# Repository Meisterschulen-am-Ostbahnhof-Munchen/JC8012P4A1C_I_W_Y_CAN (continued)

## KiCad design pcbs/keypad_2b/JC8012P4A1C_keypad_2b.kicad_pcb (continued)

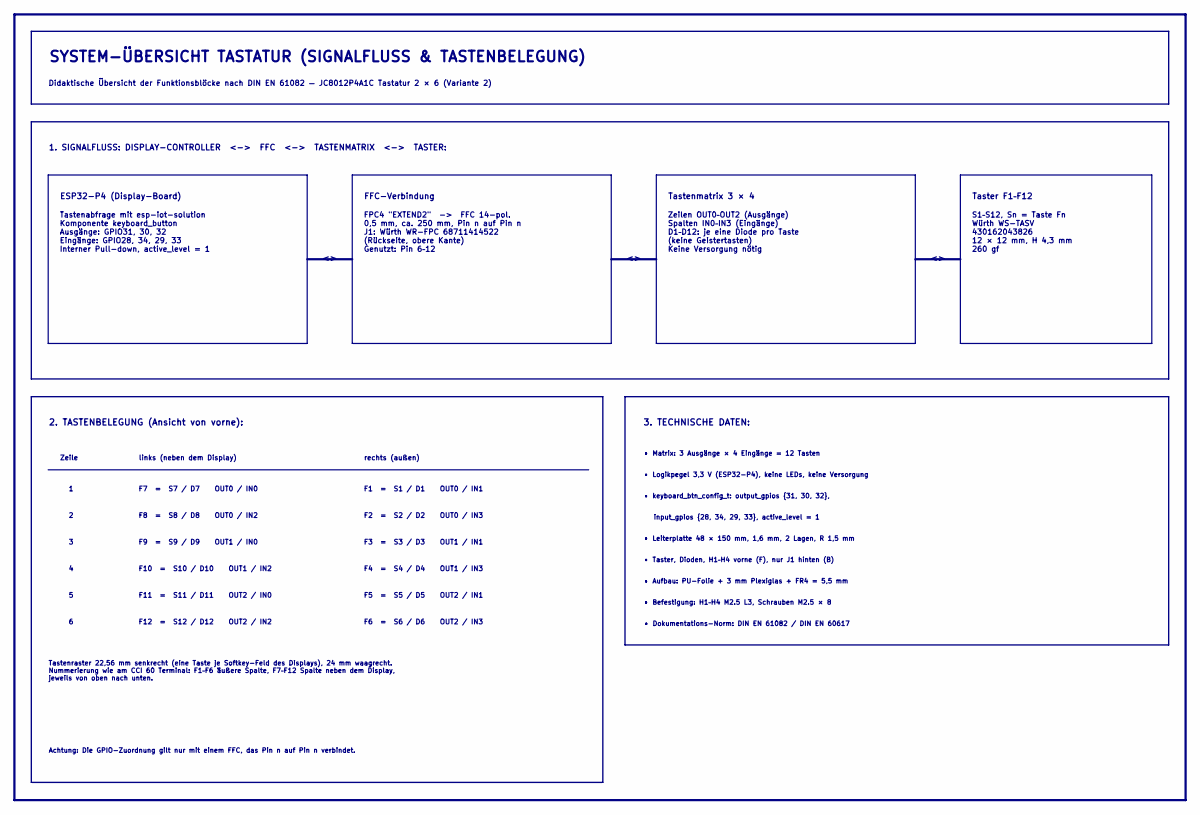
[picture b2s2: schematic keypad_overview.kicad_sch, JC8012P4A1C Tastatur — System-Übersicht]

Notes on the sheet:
• Befestigung: H1–H4 M2.5 L3, Schrauben M2.5 × 8
FPC4 "EXTEND2" -> FFC 14-pol. 0,5 mm, ca. 250 mm, Pin n auf Pin n J1: Würth WR-FPC 68711414522 (Rückseite, obere Kante) Genutzt: Pin 6–12
2. TASTENBELEGUNG (Ansicht von vorne):
F6 = S6 / D6 OUT2 / IN3
F3 = S3 / D3 OUT1 / IN1
Tastenraster 22,56 mm senkrecht (eine Taste je Softkey-Feld des Displays), 24 mm waagrecht. Nummerierung wie am CCI 60 Terminal: F1–F6 äußere Spalte, F7–F12 Spalte neben dem Display, jeweils von oben nach unten.
1. SIGNALFLUSS: DISPLAY-CONTROLLER <-> FFC <-> TASTENMATRIX <-> TASTER:
• keyboard_btn_config_t: output_gpios {31, 30, 32},
• Logikpegel 3,3 V (ESP32-P4), keine LEDs, keine Versorgung
Zeilen OUT0–OUT2 (Ausgänge) Spalten IN0–IN3 (Eingänge) D1–D12: je eine Diode pro Taste (keine Geistertasten) Keine Versorgung nötig
F5 = S5 / D5 OUT2 / IN1
F11 = S11 / D11 OUT2 / IN0
F9 = S9 / D9 OUT1 / IN0
F1 = S1 / D1 OUT0 / IN1
links (neben dem Display)
S1–S12, Sn = Taste Fn Würth WS-TASV 430162043826 12 × 12 mm, H 4,3 mm 260 gf
F12 = S12 / D12 OUT2 / IN2
Zeile
FFC-Verbindung
F4 = S4 / D4 OUT1 / IN3
• Leiterplatte 48 × 150 mm, 1,6 mm, 2 Lagen, R 1,5 mm
• Aufbau: PU-Folie + 3 mm Plexiglas + FR4 = 5,5 mm
F8 = S8 / D8 OUT0 / IN2
• Taster, Dioden, H1–H4 vorne (F), nur J1 hinten (B)
Achtung: Die GPIO-Zuordnung gilt nur mit einem FFC, das Pin n auf Pin n verbindet.
F2 = S2 / D2 OUT0 / IN3
Tastenmatrix 3 × 4
3. TECHNISCHE DATEN:
rechts (außen)
SYSTEM-ÜBERSICHT TASTATUR (SIGNALFLUSS & TASTENBELEGUNG)
• Matrix: 3 Ausgänge × 4 Eingänge = 12 Tasten
input_gpios {28, 34, 29, 33}, active_level = 1
Tastenabfrage mit esp-iot-solution Komponente keyboard_button Ausgänge: GPIO31, 30, 32 Eingänge: GPIO28, 34, 29, 33 Interner Pull-down, active_level = 1
F10 = S10 / D10 OUT1 / IN2
• Dokumentations-Norm: DIN EN 61082 / DIN EN 60617
Didaktische Übersicht der Funktionsblöcke nach DIN EN 61082 — JC8012P4A1C Tastatur 2 × 6 (Variante 2)
F7 = S7 / D7 OUT0 / IN0
Taster F1–F12
ESP32-P4 (Display-Board)

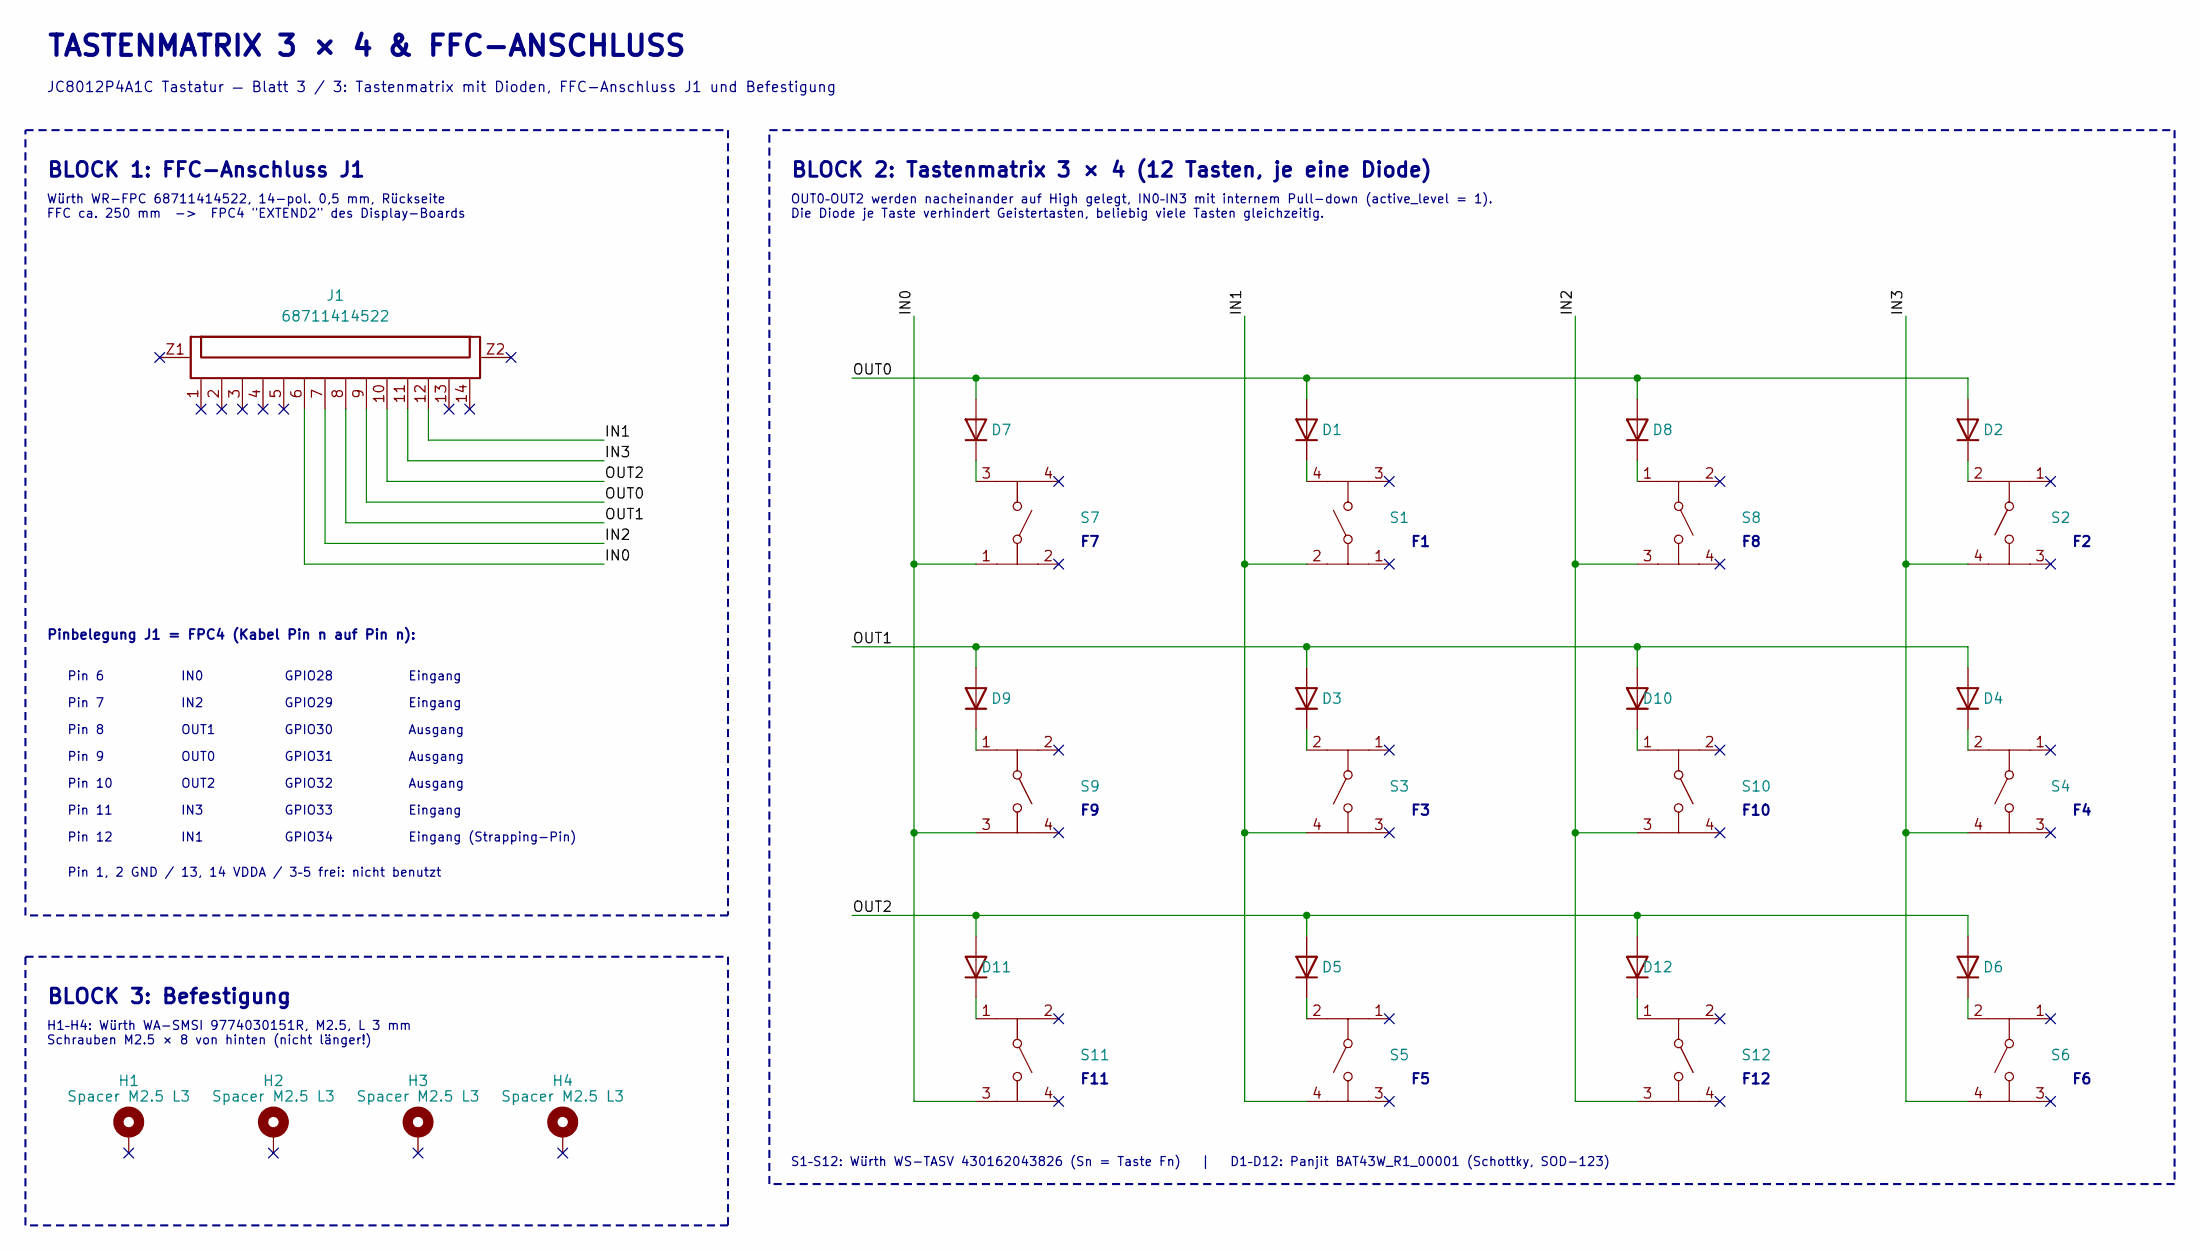
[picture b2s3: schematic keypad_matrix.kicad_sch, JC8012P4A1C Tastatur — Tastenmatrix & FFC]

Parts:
D1, D2, D3, D4, D5, D6, D7, D8, D9, D10, D11, D12: BAT43W; D_SOD-123; MPN BAT43W_R1_00001
H1, H2, H3, H4: Spacer M2.5 L3; A_Wurth_WA-SMSI_9774030151R; MPN 9774030151R
J1: 68711414522; J_Wurth_WR-FPC_68711414522; MPN 68711414522
S1, S2, S3, S4, S5, S6, S7, S8, S9, S10, S11, S12: 430162043826; SW_Wurth_WS-TASV_430162043826; MPN 430162043826

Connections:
/Tastenmatrix/IN0: J1.6, S7.1, S9.3, S11.3
/Tastenmatrix/IN1: J1.12, S1.2, S3.4, S5.4
/Tastenmatrix/IN2: J1.7, S8.3, S10.3, S12.3
/Tastenmatrix/IN3: J1.11, S2.4, S4.4, S6.4
/Tastenmatrix/OUT0: D1.2 (A), D2.2 (A), D7.2 (A), D8.2 (A), J1.9
/Tastenmatrix/OUT1: D3.2 (A), D4.2 (A), D9.2 (A), D10.2 (A), J1.8
/Tastenmatrix/OUT2: D5.2 (A), D6.2 (A), D11.2 (A), D12.2 (A), J1.10
unnamed: D1.1 (K), S1.4
unnamed: D2.1 (K), S2.2
unnamed: D3.1 (K), S3.2
unnamed: D4.1 (K), S4.2
unnamed: D5.1 (K), S5.2
unnamed: D6.1 (K), S6.2
unnamed: D7.1 (K), S7.3
unnamed: D8.1 (K), S8.1
unnamed: D9.1 (K), S9.1
unnamed: D10.1 (K), S10.1
unnamed: D11.1 (K), S11.1
unnamed: D12.1 (K), S12.1

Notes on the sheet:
GPIO29
Ausgang
BLOCK 2: Tastenmatrix 3 × 4 (12 Tasten, je eine Diode)
GPIO31
BLOCK 3: Befestigung
Pin 6
F10
OUT0
Pin 10
GPIO33
H1–H4: Würth WA-SMSI 9774030151R, M2.5, L 3 mm Schrauben M2.5 × 8 von hinten (nicht länger!)
Eingang (Strapping-Pin)
GPIO30
Eingang
GPIO32
GPIO28
IN1
Pin 12
OUT2
Pinbelegung J1 = FPC4 (Kabel Pin n auf Pin n):
Pin 8
GPIO34
F11
Pin 1, 2 GND / 13, 14 VDDA / 3–5 frei: nicht benutzt
BLOCK 1: FFC-Anschluss J1
Würth WR-FPC 68711414522, 14-pol. 0,5 mm, Rückseite FFC ca. 250 mm -> FPC4 "EXTEND2" des Display-Boards
IN3
IN2
Pin 9
Pin 11
Pin 7
OUT1
OUT0–OUT2 werden nacheinander auf High gelegt, IN0–IN3 mit internem Pull-down (active_level = 1). Die Diode je Taste verhindert Geistertasten, beliebig viele Tasten gleichzeitig.
IN0
JC8012P4A1C Tastatur — Blatt 3 / 3: Tastenmatrix mit Dioden, FFC-Anschluss J1 und Befestigung
TASTENMATRIX 3 × 4 & FFC-ANSCHLUSS
F12
S1–S12: Würth WS-TASV 430162043826 (Sn = Taste Fn) | D1–D12: Panjit BAT43W_R1_00001 (Schottky, SOD-123)

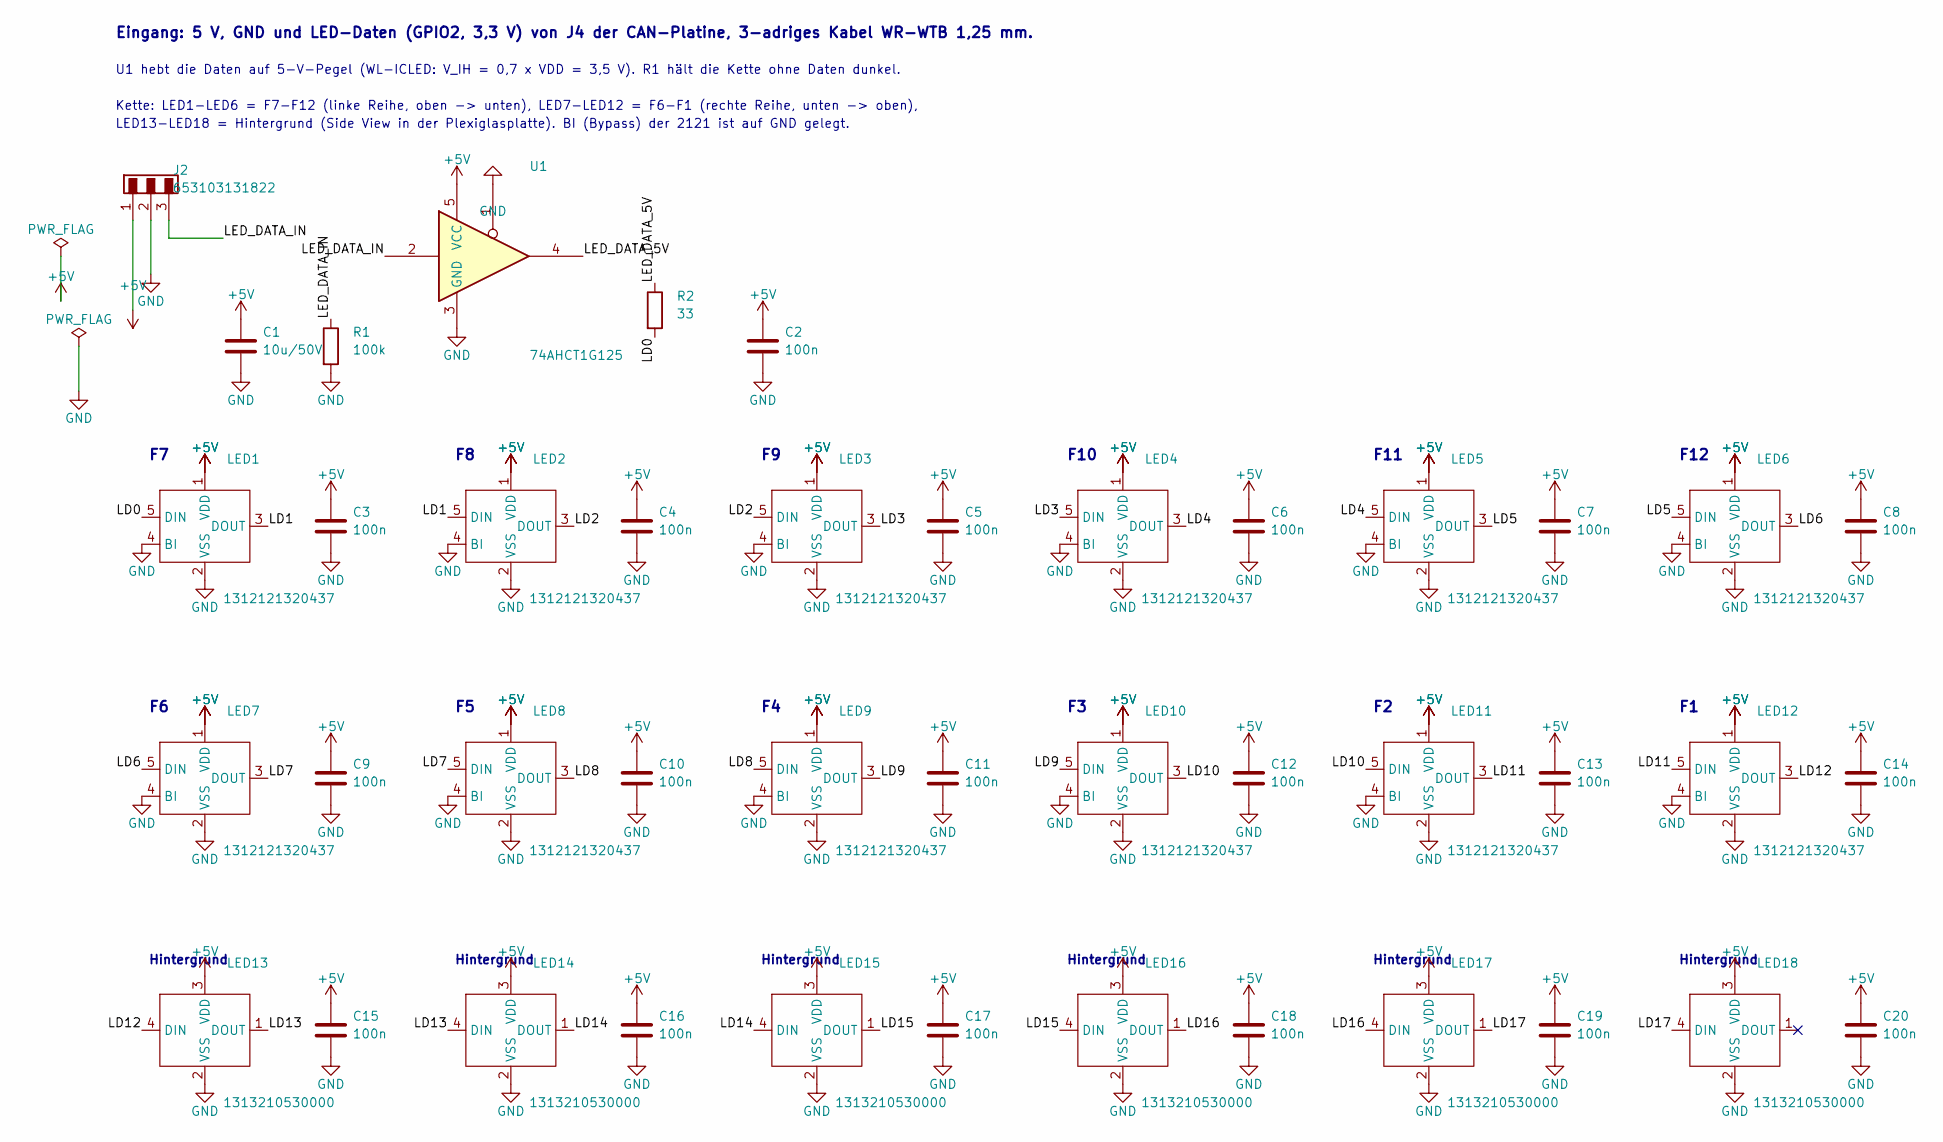
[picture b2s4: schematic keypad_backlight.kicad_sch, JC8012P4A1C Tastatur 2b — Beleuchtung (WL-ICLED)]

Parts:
C1: 10u/50V; C_1210_3225Metric; MPN 885012209073
C2, C3, C4, C5, C6, C7, C8, C9, C10, C11, C12, C13, C14, C15, C16, C17, C18, C19, C20: 100n; C_0603_1608Metric; MPN 885012206095
J2: 653103131822; J_Wurth_WR-WTB_653103131822; MPN 653103131822
LED1, LED2, LED3, LED4, LED5, LED6, LED7, LED8, LED9, LED10, LED11, LED12: 1312121320437; U_Wurth_WL-ICLED_1312121320437; MPN 1312121320437
LED13, LED14, LED15, LED16, LED17, LED18: 1313210530000; U_Wurth_WL-ICLED_1313210530000; MPN 1313210530000
R1: 100k; R_0603_1608Metric; MPN RC0603FR-07100KL
R2: 33; R_0603_1608Metric; MPN RC0603FR-0733RL
U1: 74AHCT1G125; SOT-23-5; MPN SN74AHCT1G125DBVR

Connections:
+5V: C1.1, C2.1, C3.1, C4.1, C5.1, C6.1, C7.1, C8.1, C9.1, C10.1, C11.1, C12.1, C13.1, C14.1, C15.1, C16.1, C17.1, C18.1, C19.1, C20.1, J2.1, LED1.1 (VDD), LED1.6 (VDD), LED2.1 (VDD), LED2.6 (VDD), LED3.1 (VDD), LED3.6 (VDD), LED4.1 (VDD), LED4.6 (VDD), LED5.1 (VDD), LED5.6 (VDD), LED6.1 (VDD), LED6.6 (VDD), LED7.1 (VDD), LED7.6 (VDD), LED8.1 (VDD), LED8.6 (VDD), LED9.1 (VDD), LED9.6 (VDD), LED10.1 (VDD), LED10.6 (VDD), LED11.1 (VDD), LED11.6 (VDD), LED12.1 (VDD), LED12.6 (VDD), LED13.3 (VDD), LED14.3 (VDD), LED15.3 (VDD), LED16.3 (VDD), LED17.3 (VDD), LED18.3 (VDD), U1.5 (VCC)
/Beleuchtung/LD0: LED1.5 (DIN), R2.2
/Beleuchtung/LD1: LED1.3 (DOUT), LED2.5 (DIN)
/Beleuchtung/LD2: LED2.3 (DOUT), LED3.5 (DIN)
/Beleuchtung/LD3: LED3.3 (DOUT), LED4.5 (DIN)
/Beleuchtung/LD4: LED4.3 (DOUT), LED5.5 (DIN)
/Beleuchtung/LD5: LED5.3 (DOUT), LED6.5 (DIN)
/Beleuchtung/LD6: LED6.3 (DOUT), LED7.5 (DIN)
/Beleuchtung/LD7: LED7.3 (DOUT), LED8.5 (DIN)
/Beleuchtung/LD8: LED8.3 (DOUT), LED9.5 (DIN)
/Beleuchtung/LD9: LED9.3 (DOUT), LED10.5 (DIN)
/Beleuchtung/LD10: LED10.3 (DOUT), LED11.5 (DIN)
/Beleuchtung/LD11: LED11.3 (DOUT), LED12.5 (DIN)
/Beleuchtung/LD12: LED12.3 (DOUT), LED13.4 (DIN)
/Beleuchtung/LD13: LED13.1 (DOUT), LED14.4 (DIN)
/Beleuchtung/LD14: LED14.1 (DOUT), LED15.4 (DIN)
/Beleuchtung/LD15: LED15.1 (DOUT), LED16.4 (DIN)
/Beleuchtung/LD16: LED16.1 (DOUT), LED17.4 (DIN)
/Beleuchtung/LD17: LED17.1 (DOUT), LED18.4 (DIN)
/Beleuchtung/LED_DATA_5V: R2.1, U1.4
/Beleuchtung/LED_DATA_IN: J2.3, R1.1, U1.2
GND: C1.2, C2.2, C3.2, C4.2, C5.2, C6.2, C7.2, C8.2, C9.2, C10.2, C11.2, C12.2, C13.2, C14.2, C15.2, C16.2, C17.2, C18.2, C19.2, C20.2, J2.2, LED1.2 (VSS), LED1.4 (BI), LED2.2 (VSS), LED2.4 (BI), LED3.2 (VSS), LED3.4 (BI), LED4.2 (VSS), LED4.4 (BI), LED5.2 (VSS), LED5.4 (BI), LED6.2 (VSS), LED6.4 (BI), LED7.2 (VSS), LED7.4 (BI), LED8.2 (VSS), LED8.4 (BI), LED9.2 (VSS), LED9.4 (BI), LED10.2 (VSS), LED10.4 (BI), LED11.2 (VSS), LED11.4 (BI), LED12.2 (VSS), LED12.4 (BI), LED13.2 (VSS), LED14.2 (VSS), LED15.2 (VSS), LED16.2 (VSS), LED17.2 (VSS), LED18.2 (VSS), R1.2, U1.1, U1.3 (GND)

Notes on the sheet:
Eingang: 5 V, GND und LED-Daten (GPIO2, 3,3 V) von J4 der CAN-Platine, 3-adriges Kabel WR-WTB 1,25 mm.
U1 hebt die Daten auf 5-V-Pegel (WL-ICLED: V_IH = 0,7 x VDD = 3,5 V). R1 hält die Kette ohne Daten dunkel.
Kette: LED1-LED6 = F7-F12 (linke Reihe, oben -> unten), LED7-LED12 = F6-F1 (rechte Reihe, unten -> oben),
LED13-LED18 = Hintergrund (Side View in der Plexiglasplatte). BI (Bypass) der 2121 ist auf GND gelegt.
F10
F11
F12
Hintergrund

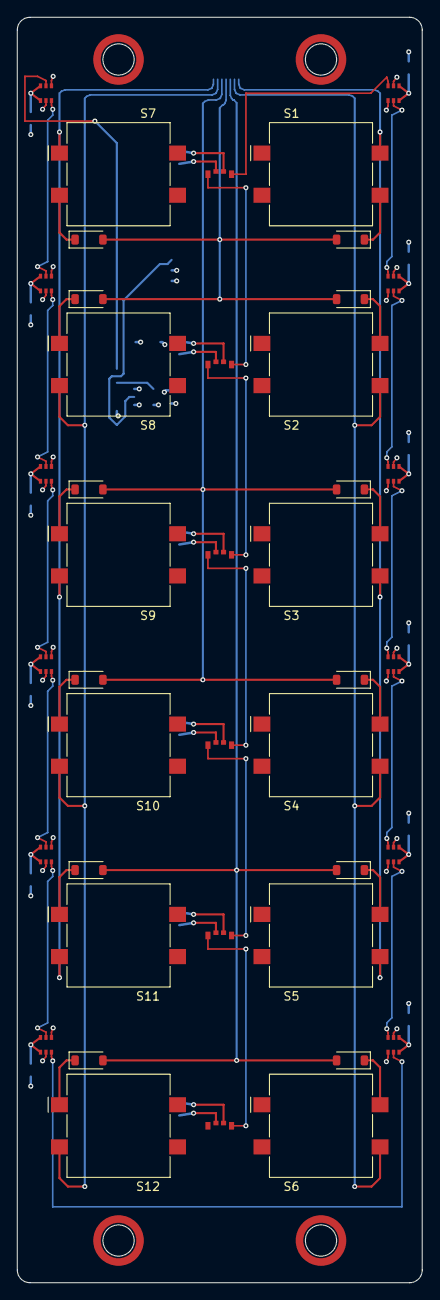
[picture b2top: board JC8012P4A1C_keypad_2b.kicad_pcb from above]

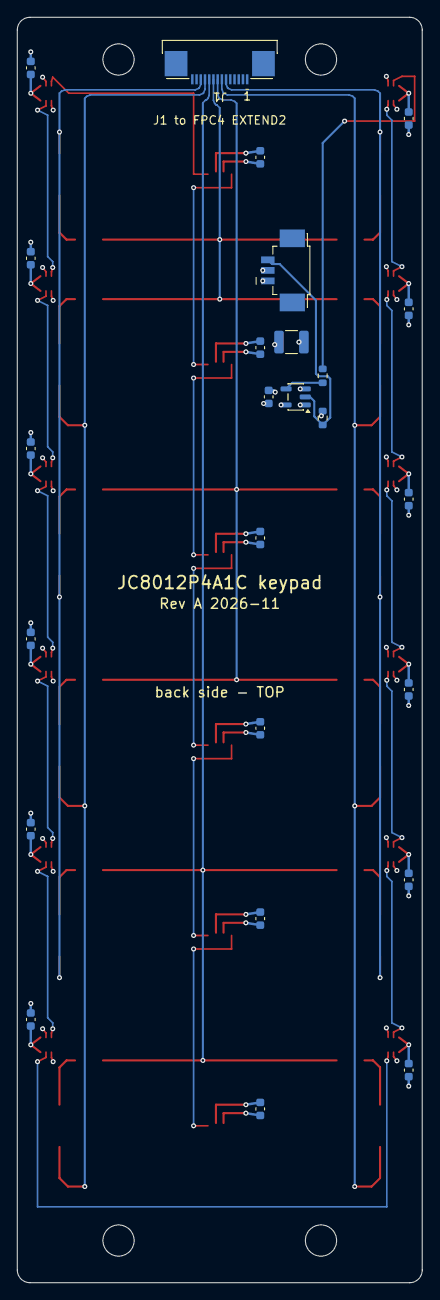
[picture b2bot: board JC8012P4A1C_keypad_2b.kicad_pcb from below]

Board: 4 copper layers, 48.0 x 150.0 mm, 71 parts (25 on the bottom side), 41 nets.

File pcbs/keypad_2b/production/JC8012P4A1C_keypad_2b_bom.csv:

"Reference","Qty","Value","Manufacturer","MPN","Footprint","DNP"
"C1","1","10u/50V","Wurth Elektronik","885012209073","Capacitor_SMD:C_1210_3225Metric",""
"C2-C20","19","100n","Wurth Elektronik","885012206095","Capacitor_SMD:C_0603_1608Metric",""
"D1-D12","12","BAT43W","Panjit","BAT43W_R1_00001","Diode_SMD:D_SOD-123",""
"H1-H4","4","Spacer M2.5 L3","Wurth Elektronik","9774030151R","Keypad:A_Wurth_WA-SMSI_9774030151R",""
"J1","1","68711414522","Wurth Elektronik","68711414522","Keypad:J_Wurth_WR-FPC_68711414522",""
"J2","1","653103131822","Wurth Elektronik","653103131822","Keypad:J_Wurth_WR-WTB_653103131822",""
"LED1-LED12","12","1312121320437","Wurth Elektronik","1312121320437","Keypad:U_Wurth_WL-ICLED_1312121320437",""
"LED13-LED18","6","1313210530000","Wurth Elektronik","1313210530000","Keypad:U_Wurth_WL-ICLED_1313210530000",""
"R1","1","100k","Yageo","RC0603FR-07100KL","Resistor_SMD:R_0603_1608Metric",""
"R2","1","33","Yageo","RC0603FR-0733RL","Resistor_SMD:R_0603_1608Metric",""
"S1-S12","12","430162043826","Wurth Elektronik","430162043826","Keypad:SW_Wurth_WS-TASV_430162043826",""
"U1","1","74AHCT1G125","Texas Instruments","SN74AHCT1G125DBVR","Package_TO_SOT_SMD:SOT-23-5",""
